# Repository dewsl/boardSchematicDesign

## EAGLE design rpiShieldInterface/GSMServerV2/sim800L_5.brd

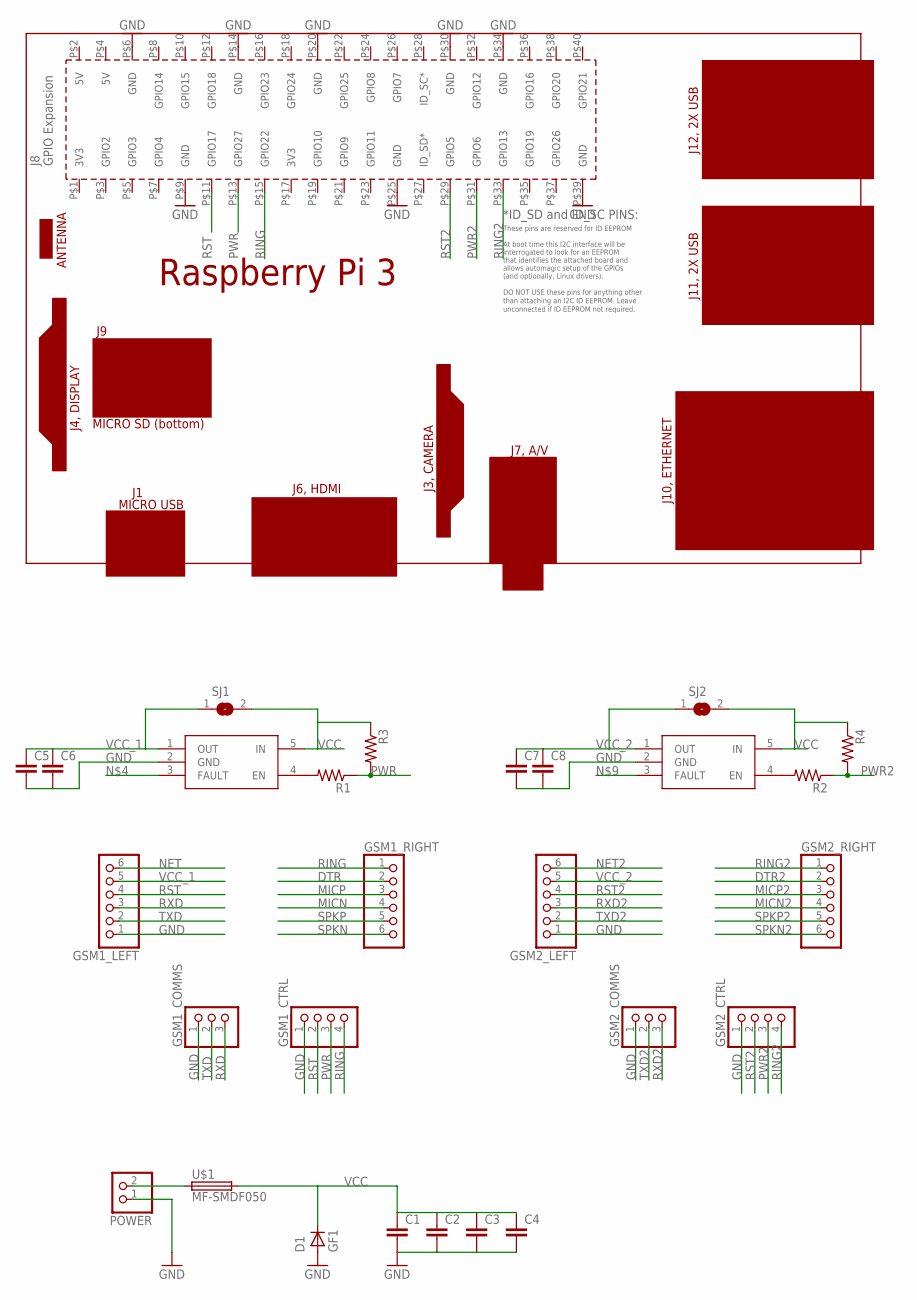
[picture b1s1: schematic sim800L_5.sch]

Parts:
C1, C2, C3, C4: C-EUC1210; C1210
C5, C6, C7, C8: C-EUC4532; C4532
D1: GF1; SMA-DO214AC
GSM1_COMMS, GSM2_COMMS: PINHD-1X3; 1X03
GSM1_CTRL, GSM2_CTRL: PINHD-1X4; 1X04
GSM1_LEFT, GSM1_RIGHT, GSM2_LEFT, GSM2_RIGHT: PINHD-1X6; 1X06
POWER: PINHD-1X2; 1X02
R1, R2, R3, R4: R-US_R0805; R0805
SJ1, SJ2: SJ
U$1: MF-SMDF050
U$2: RPI3_SHIELD
U$3, U$4: STMPS2161STR; SOT23-5L

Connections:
DTR: GSM1_RIGHT.2
DTR2: GSM2_RIGHT.2
GND: C1.2, C2.2, C3.2, C4.2, C5.2, C6.2, C7.2, C8.2, D1.A, GSM1_COMMS.1, GSM1_CTRL.1, GSM1_LEFT.1, GSM2_COMMS.1, GSM2_CTRL.1, GSM2_LEFT.1, POWER.1, U$2.P$6 (GND), U$2.P$9 (GND), U$2.P$14 (GND), U$2.P$20 (GND), U$2.P$25 (GND), U$2.P$30 (GND), U$2.P$34 (GND), U$2.P$39 (GND), U$3.2 (GND), U$4.2 (GND)
MICN: GSM1_RIGHT.4
MICN2: GSM2_RIGHT.4
MICP: GSM1_RIGHT.3
MICP2: GSM2_RIGHT.3
unnamed: POWER.2, U$1.1
unnamed: R1.2, U$4.4 (EN)
unnamed: R2.2, U$3.4 (EN)
NET: GSM1_LEFT.6
NET2: GSM2_LEFT.6
PWR: GSM1_CTRL.3, R1.1, R3.2, U$2.P$13 (GPIO27)
PWR2: GSM2_CTRL.3, R2.1, R4.2, U$2.P$31 (GPIO6)
RING: GSM1_CTRL.4, GSM1_RIGHT.1, U$2.P$15 (GPIO22)
RING2: GSM2_CTRL.4, GSM2_RIGHT.1, U$2.P$33 (GPIO13)
RST: GSM1_CTRL.2, GSM1_LEFT.4, U$2.P$11 (GPIO17)
RST2: GSM2_CTRL.2, GSM2_LEFT.4, U$2.P$29 (GPIO5)
RXD: GSM1_COMMS.3, GSM1_LEFT.3
RXD2: GSM2_COMMS.3, GSM2_LEFT.3
SPKN: GSM1_RIGHT.6
SPKN2: GSM2_RIGHT.6
SPKP: GSM1_RIGHT.5
SPKP2: GSM2_RIGHT.5
TXD: GSM1_COMMS.2, GSM1_LEFT.2
TXD2: GSM2_COMMS.2, GSM2_LEFT.2
VCC: C1.1, C2.1, C3.1, C4.1, D1.K (C), R3.1, R4.1, SJ1.2, SJ2.2, U$1.2, U$3.5 (IN), U$4.5 (IN)
VCC_1: C5.1, C6.1, GSM1_LEFT.5, SJ1.1, U$4.1 (OUT)
VCC_2: C7.1, C8.1, GSM2_LEFT.5, SJ2.1, U$3.1 (OUT)

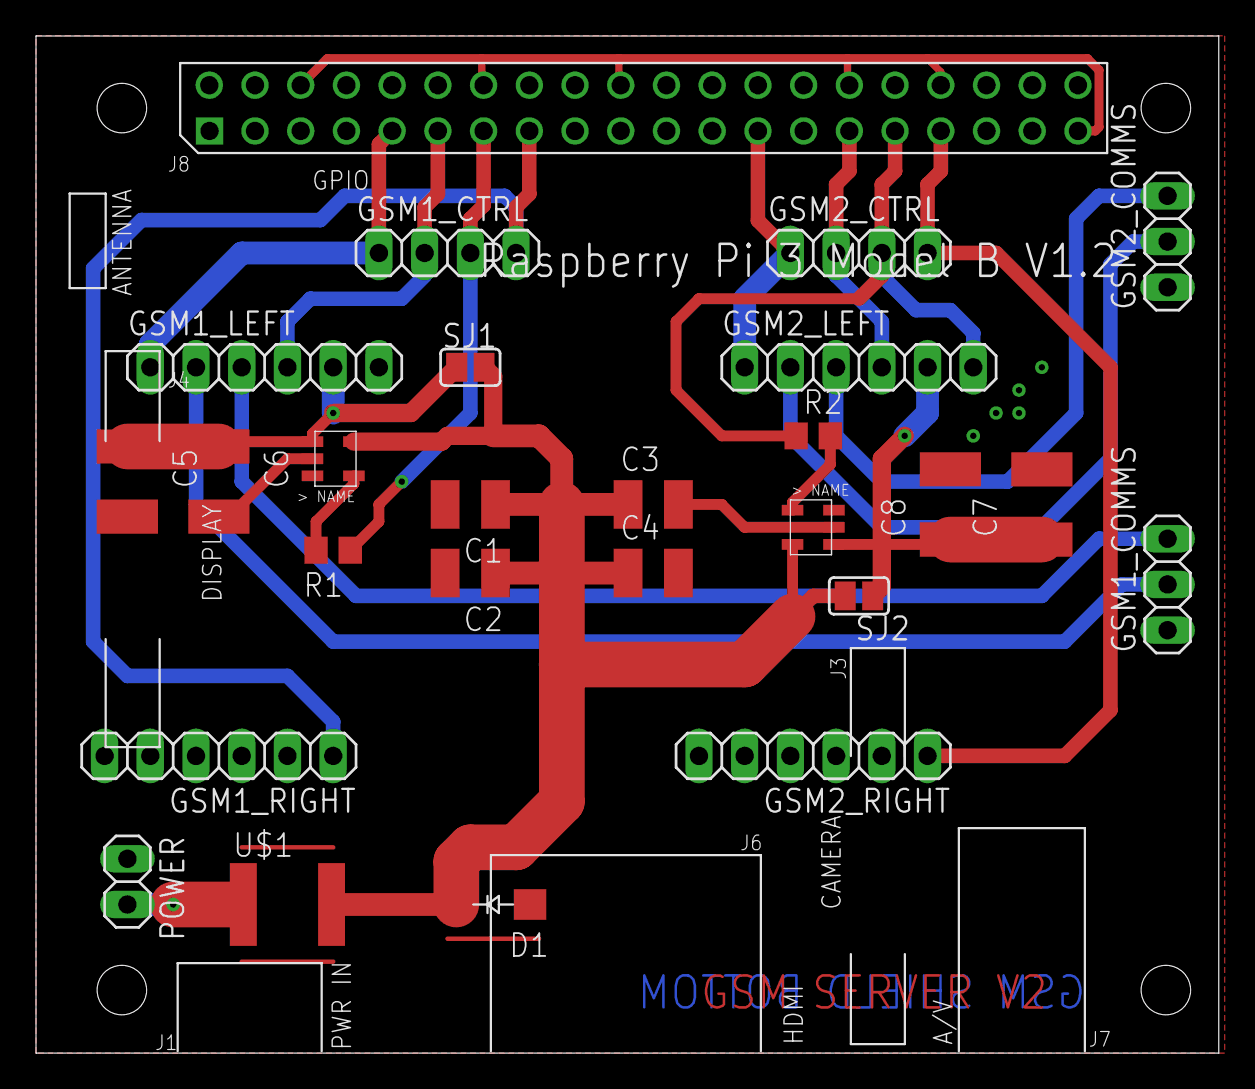
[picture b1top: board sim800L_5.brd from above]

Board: 2 copper layers, 65.7 x 56.5 mm, 26 parts (0 on the bottom side), 17 nets.
